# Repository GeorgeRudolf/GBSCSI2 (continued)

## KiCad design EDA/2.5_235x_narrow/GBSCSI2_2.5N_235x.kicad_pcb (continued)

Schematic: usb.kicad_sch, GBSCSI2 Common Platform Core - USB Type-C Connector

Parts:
C8: 100nF; C_0402_1005Metric; LCSC C307331
J3: GCT-4105; USB_C_Receptacle_HRO_TYPE-C-31-M-12; LCSC C2927038
R23, R24: 5.1kΩ; R_0402_1005Metric; LCSC C25905
U3: USB TVS; SOT-23-6; LCSC C2827654

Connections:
/Core Logic, Basic Controls/D+: J3.A6 (D+), J3.B6 (D+), U3.3 (I/O2), U3.4 (I/O2); also elsewhere on the board
/Core Logic, Basic Controls/D-: J3.A7 (D-), J3.B7 (D-), U3.1 (I/O1), U3.6 (I/O1); also elsewhere on the board
/Core Logic, Basic Controls/USB/CC1: J3.A5 (CC1), R24.1
/Core Logic, Basic Controls/USB/CC2: J3.B5 (CC2), R23.1
GND: C8.2, J3.A1 (GND), J3.A12 (GND), J3.B1 (GND), J3.B12 (GND), J3.S1 (SHIELD), R23.2, R24.2, U3.2 (GND); also elsewhere on the board
VBUS: C8.1, J3.A4 (VBUS), J3.A9 (VBUS), J3.B4 (VBUS), J3.B9 (VBUS), U3.5 (VBUS); also elsewhere on the board

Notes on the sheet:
USB-C Spec §3.2.1¶11

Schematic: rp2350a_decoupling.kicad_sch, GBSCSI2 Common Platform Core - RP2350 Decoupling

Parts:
C9, C11, C13, C14, C15, C16, C17, C18, C19: 100nF; C_0402_1005Metric; LCSC C307331
C10: 4.7μF; C_0402_1005Metric; LCSC C23733
C12: 1μF; C_0402_1005Metric; LCSC C52923

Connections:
+1.1V: C9.1, C10.1, C11.1; also elsewhere on the board
+3.3V: C12.1, C13.1, C14.1, C15.1, C16.1, C17.1, C18.1, C19.1; also elsewhere on the board
GND: C9.2, C10.2, C11.2, C12.2, C13.2, C14.2, C15.2, C16.2, C17.2, C18.2, C19.2; also elsewhere on the board

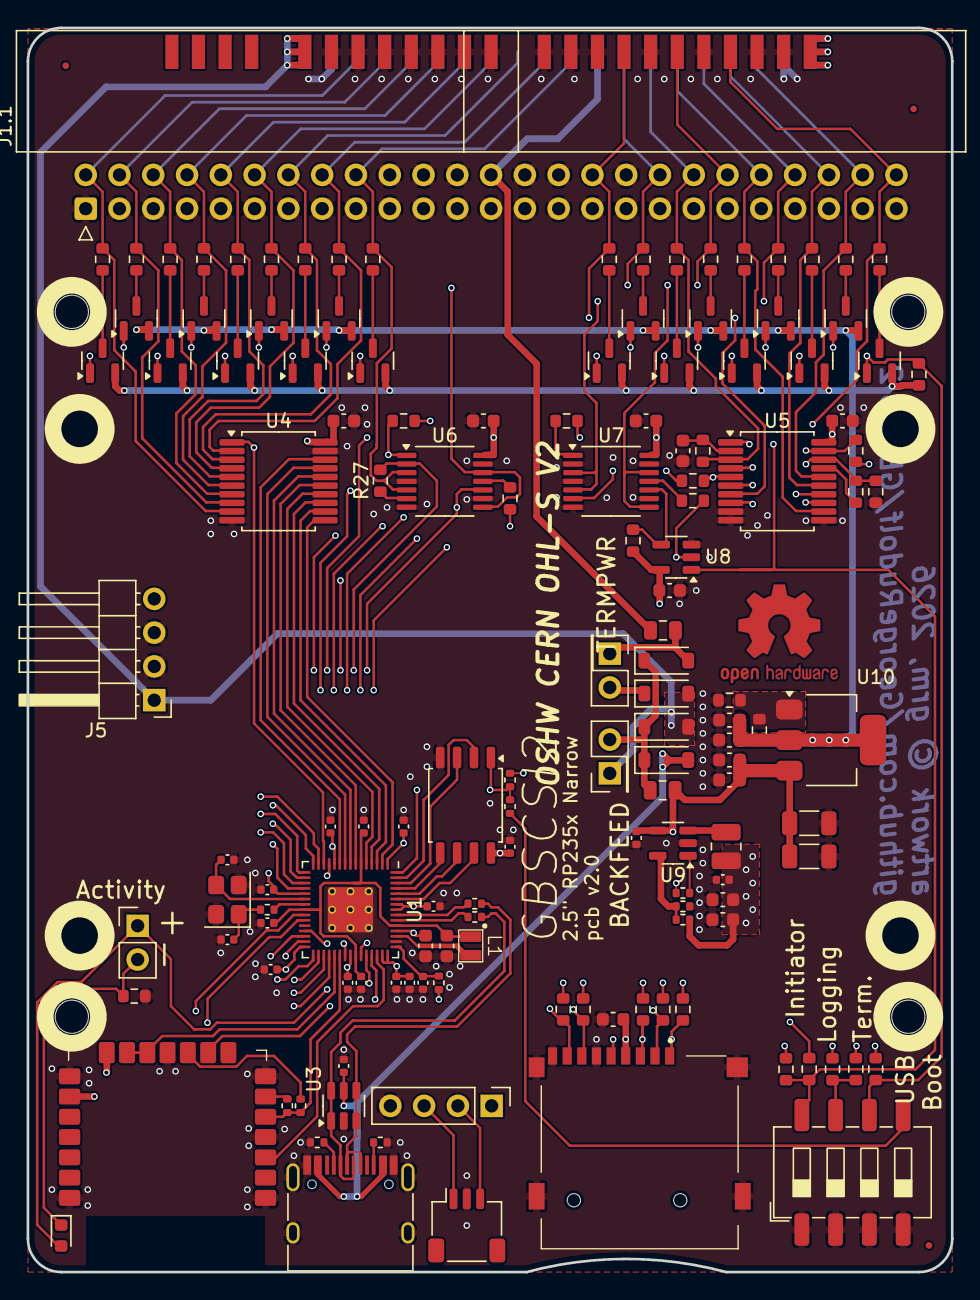
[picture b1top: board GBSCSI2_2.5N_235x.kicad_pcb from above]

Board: 4 copper layers, 69.5 x 93.5 mm, 145 parts (0 on the bottom side), 114 nets.

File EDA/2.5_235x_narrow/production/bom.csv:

Designator,Footprint,Quantity,Value,LCSC Part #
"C1, C4",0603,2,4.7μF,C19666
"C10, C27, C5",0402,3,4.7μF,C23733
"C11, C13, C14, C15, C16, C17, C18, C19, C28, C6, C8, C9",0402,12,100nF,C307331
C12,0402,1,1μF,C52923
"C2, C3",0402,2,15pF,C1548
"C20, C35",1206,2,47μF,C96123
C21,0603,1,12pF,C38523
"C22, C23, C24, C25, C26, C32, C33",0603,7,100nF,C14663
"C29, C30, C7",0603,3,10μF,C96446
"C31, C34",0603,2,1μF,C15849
"D1, D2, D3, D4",D_SOD-123,4,1N5819,C82544
D5,0603,1,YELLOW,C72038
"F1, F2",0805,2,1A,C468888
FID1,Fiducial_0.5mm_Mask1mm,1,Fiducial,N/A
J1,PinHeader_2x25-2_P2.00mm_straddle,1,SCSI_50-2P_2mm,N/A
J1.1,IDC-Header_2x25_P2.54mm_Horizontal,1,SCSI_50P_2.54mm,N/A
J2,TF01A,1,TF003,C5155563 
J3,USB_C_Receptacle_HRO_TYPE-C-31-M-12,1,GCT-4105,C2927038
J4,JST_SH_SM03B-SRSS-TB_1x03-1MP_P1.00mm_Horizontal,1,SM03B-SRSS-TB,C160403
J4.1,PinHeader_1x04_P2.54mm_Vertical,1,Conn_01x04,N/A
J5,PinHeader_1x04_P2.54mm_Horizontal,1,Conn_01x04,N/A
J6,PinHeader_1x02_P2.54mm_Vertical,1,Conn_01x02,N/A
"JP1, JP2",PinHeader_2x01_P2.54mm_Vertical,2,Jumper_2_Open,N/A
L1,L_Abracon_AOTA-B2016,1,3.3μH,C42411119
L2,1008,1,1μH,C5832356
M1,RPi_RM2,1,~,N/A
"Q1, Q10, Q11, Q12, Q13, Q14, Q15, Q16, Q17, Q18, Q2, Q3, Q4, Q5, Q6, Q7, Q8, Q9",SOT-23,18,AO3401A,C15127
"R1, R4",0402,2,1kΩ,C11702
"R10, R11, R12, R18, R19, R20, R21, R22, R29, R5, R6, R7, R8, R9",0603,14,4.7kΩ,C23162
"R13, R14, R17, R26, R27, R28, R30, R55",0603,8,1kΩ,C21190
"R15, R16, R3",0402,3,22Ω,C25092
R2,0402,1,4.7kΩ,C25900
"R23, R24",0402,2,5.1kΩ,C25905
"R25, R31, R32, R33, R34, R35, R36, R37, R38, R39, R40, R41, R42, R43, R44, R45, R46, R47, R48",0603,19,110Ω,C22781
"R49, R54",0402,2,10kΩ,C25744
R50,0402,1,442kΩ,C5101
R51,0402,1,100kΩ,C25741
R52,0603,1,0Ω,C21189
R53,0603,1,~,N/A
R56,0402,1,470Ω,
SW1,SW_DIP_SPSTx04_Slide_6.7x11.72mm_W8.61mm_P2.54mm_LowProfile,1,SW_DIP_x04,C5160841
U1,RP2350-QFN-60-1EP_7x7_P0.4mm_EP3.4x3.4mm_ThermalVias,1,RP235x_60QFN,C41378174
U10,SOT-223-3_TabPin2,1,AZ1117-2.85,C14791
U2,SOIC-8_5.23x5.23mm_P1.27mm,1,W25Q128JVS,C97521
U3,SOT-23-6,1,USB TVS,C2827654
"U4, U5",SSOP-20_5.3x7.2mm_P0.65mm,2,74LVTH245,C2652121
"U6, U7",TSSOP-14_4.4x5mm_P0.65mm,2,74LVTH125,C7042
U8,SOT-23-5,1,SN74AHC1G125DBVR,C7468
U9,SOT-23-5,1,TLV62569DBV,C141836
Y1,Crystal_SMD_3225-4Pin_3.2x2.5mm,1,12MHz,C20625731

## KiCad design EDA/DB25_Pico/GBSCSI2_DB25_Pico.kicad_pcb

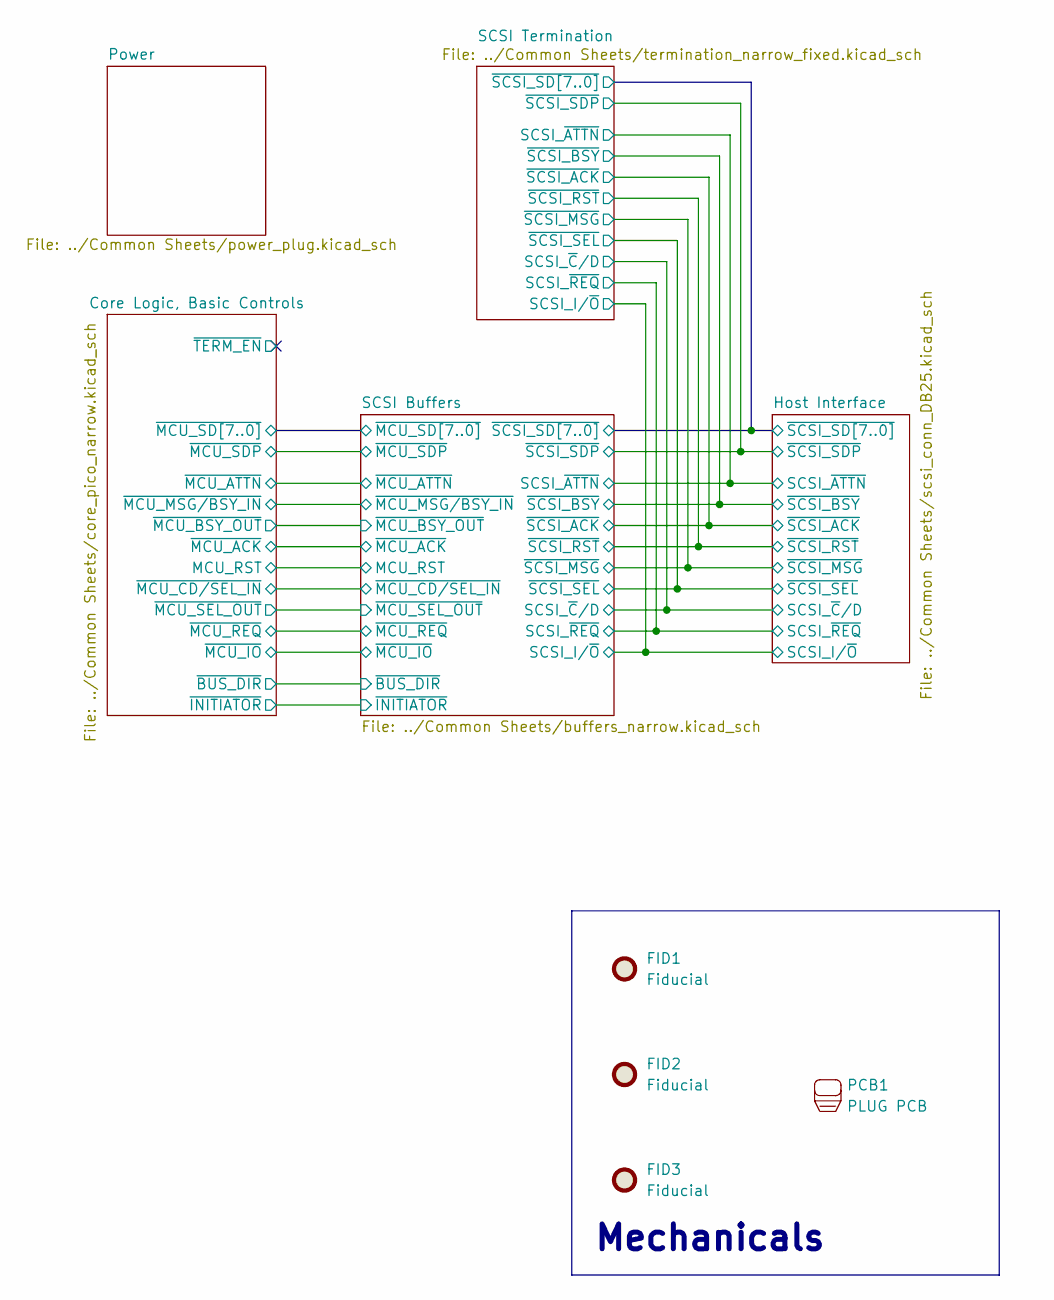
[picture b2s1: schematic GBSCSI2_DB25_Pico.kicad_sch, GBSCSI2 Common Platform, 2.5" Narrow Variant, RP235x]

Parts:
FID1, FID2, FID3: Fiducial; Fiducial_0.5mm_Mask1mm; LCSC N/A
PCB1: PLUG PCB; GBSCSI2_PLUG_PCB

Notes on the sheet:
Mechanicals

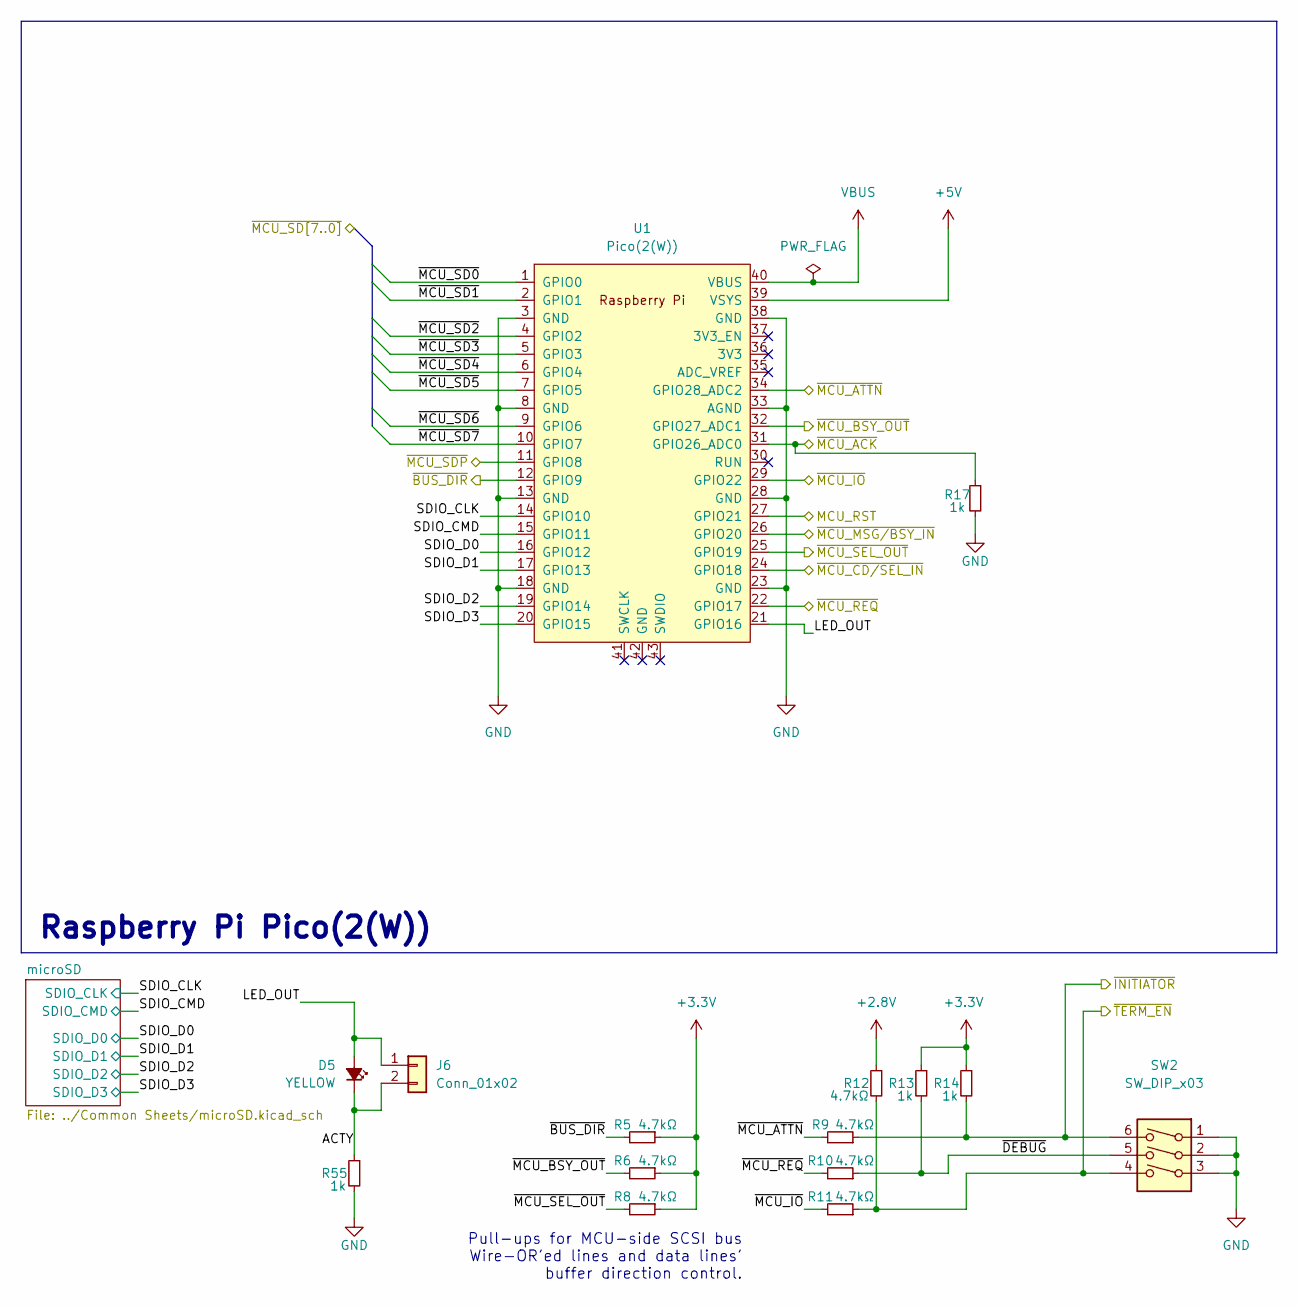
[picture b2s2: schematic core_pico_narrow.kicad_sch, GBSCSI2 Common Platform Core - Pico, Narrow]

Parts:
D5: YELLOW; LED_0603_1608Metric; LCSC C72038
J6: Conn_01x02; PinHeader_1x02_P2.54mm_Vertical; LCSC N/A
R5, R6, R8, R9, R10, R11, R12: 4.7kΩ; R_0603_1608Metric; LCSC C23162
R13, R14, R17, R55: 1k; R_0603_1608Metric; LCSC C21190
SW2: SW_DIP_x03; SW_DIP_SPSTx03_Slide_6.7x9.18mm_W8.61mm_P2.54mm_LowProfile; LCSC C2842910
U1: Pico(2(W)); RPi_Pico_W_SMD; LCSC C7203003

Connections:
+2.8V: R12.1; also elsewhere on the board
+3.3V: R5.1, R6.1, R8.1, R13.1, R14.1; also elsewhere on the board
+5V: U1.39 (VSYS); also elsewhere on the board
/Core Logic, Basic Controls/ACTY: D5.1 (K), J6.2, R55.1
/Core Logic, Basic Controls/LED_OUT: D5.2 (A), J6.1, U1.21 (GPIO16)
/Core Logic, Basic Controls/MCU_RST: U1.27 (GPIO21); also elsewhere on the board
/Core Logic, Basic Controls/SDIO_CLK: U1.14 (GPIO10); also elsewhere on the board
/Core Logic, Basic Controls/SDIO_CMD: U1.15 (GPIO11); also elsewhere on the board
/Core Logic, Basic Controls/SDIO_D0: U1.16 (GPIO12); also elsewhere on the board
/Core Logic, Basic Controls/SDIO_D1: U1.17 (GPIO13); also elsewhere on the board
/Core Logic, Basic Controls/SDIO_D2: U1.19 (GPIO14); also elsewhere on the board
/Core Logic, Basic Controls/SDIO_D3: U1.20 (GPIO15); also elsewhere on the board
/Core Logic, Basic Controls/~BUS_DIR: R5.2, U1.12 (GPIO9); also elsewhere on the board
/Core Logic, Basic Controls/~DEBUG: R10.1, R13.2, SW2.5
/Core Logic, Basic Controls/~INITIATOR: R9.1, R14.2, SW2.6; also elsewhere on the board
/Core Logic, Basic Controls/~MCU_ACK: R17.1, U1.31 (GPIO26_ADC0); also elsewhere on the board
/Core Logic, Basic Controls/~MCU_ATTN: R9.2, U1.34 (GPIO28_ADC2); also elsewhere on the board
/Core Logic, Basic Controls/~MCU_BSY_OUT: R6.2, U1.32 (GPIO27_ADC1); also elsewhere on the board
/Core Logic, Basic Controls/~MCU_CD/SEL_IN: U1.24 (GPIO18); also elsewhere on the board
/Core Logic, Basic Controls/~MCU_IO: R11.2, U1.29 (GPIO22); also elsewhere on the board
/Core Logic, Basic Controls/~MCU_MSG/BSY_IN: U1.26 (GPIO20); also elsewhere on the board
/Core Logic, Basic Controls/~MCU_REQ: R10.2, U1.22 (GPIO17); also elsewhere on the board
/Core Logic, Basic Controls/~MCU_SD0: U1.1 (GPIO0); also elsewhere on the board
/Core Logic, Basic Controls/~MCU_SD1: U1.2 (GPIO1); also elsewhere on the board
/Core Logic, Basic Controls/~MCU_SD2: U1.4 (GPIO2); also elsewhere on the board
/Core Logic, Basic Controls/~MCU_SD3: U1.5 (GPIO3); also elsewhere on the board
/Core Logic, Basic Controls/~MCU_SD4: U1.6 (GPIO4); also elsewhere on the board
/Core Logic, Basic Controls/~MCU_SD5: U1.7 (GPIO5); also elsewhere on the board
/Core Logic, Basic Controls/~MCU_SD6: U1.9 (GPIO6); also elsewhere on the board
/Core Logic, Basic Controls/~MCU_SD7: U1.10 (GPIO7); also elsewhere on the board
/Core Logic, Basic Controls/~MCU_SDP: U1.11 (GPIO8); also elsewhere on the board
/Core Logic, Basic Controls/~MCU_SEL_OUT: R8.2, U1.25 (GPIO19); also elsewhere on the board
/Core Logic, Basic Controls/~TERM_EN: R11.1, R12.2, SW2.4
GND: R17.2, R55.2, SW2.1, SW2.2, SW2.3, U1.3 (GND), U1.8 (GND), U1.13 (GND), U1.18 (GND), U1.23 (GND), U1.28 (GND), U1.33 (AGND), U1.38 (GND); also elsewhere on the board
VBUS: U1.40 (VBUS); also elsewhere on the board

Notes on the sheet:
Pull-ups for MCU-side SCSI bus Wire-OR'ed lines and data lines' buffer direction control.
Raspberry Pi Pico(2(W))

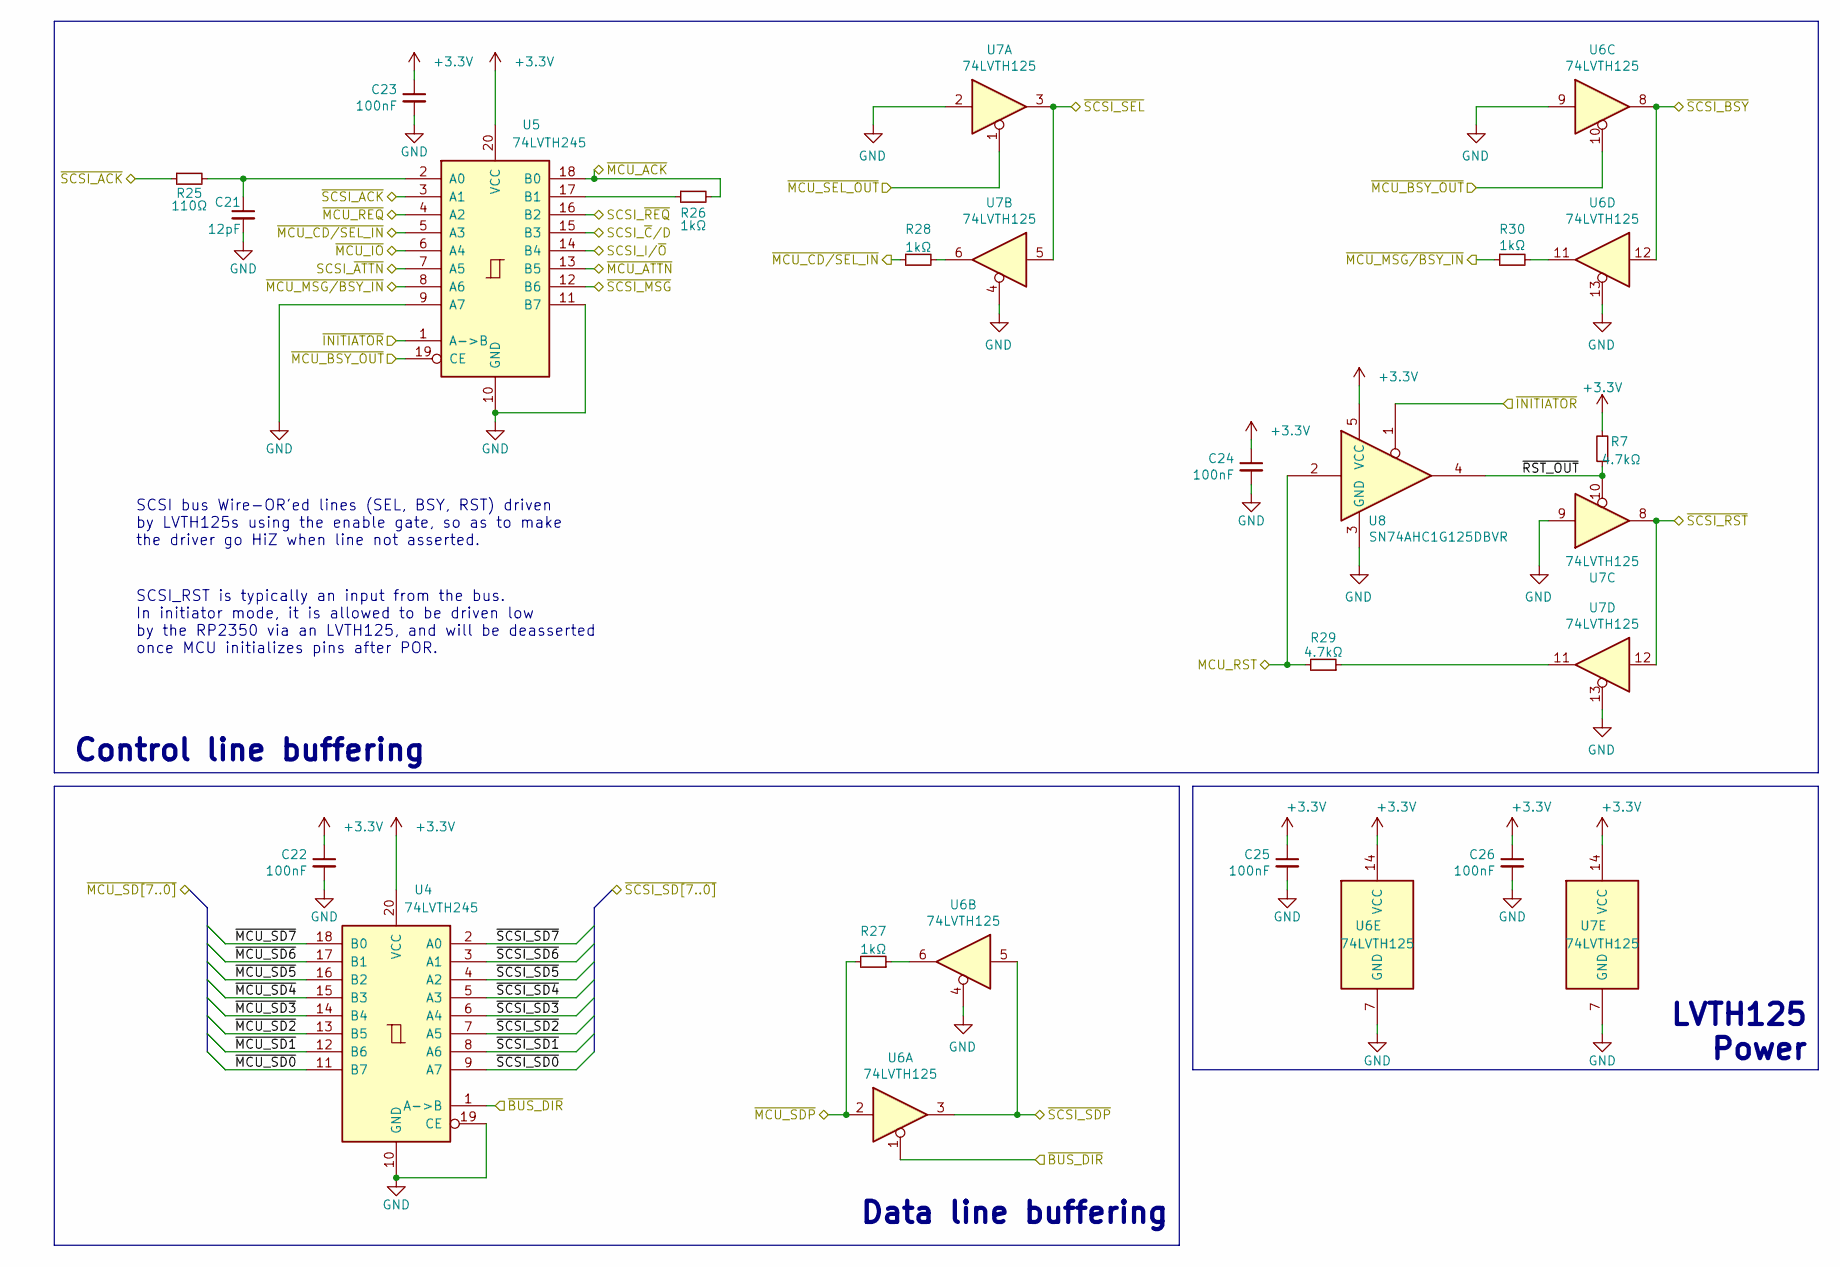
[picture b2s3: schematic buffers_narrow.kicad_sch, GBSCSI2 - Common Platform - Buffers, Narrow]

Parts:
C21: 12pF; C_0603_1608Metric; LCSC C38523
C22, C23, C24, C25, C26: 100nF; C_0603_1608Metric; LCSC C14663
R7, R29: 4.7kΩ; R_0603_1608Metric; LCSC C23162
R25: 110Ω; R_0603_1608Metric; LCSC C22781
R26, R27, R28, R30: 1kΩ; R_0603_1608Metric; LCSC C21190
U4, U5: 74LVTH245; SSOP-20_5.3x7.2mm_P0.65mm; LCSC C2652121
U6, U7: 74LVTH125; TSSOP-14_4.4x5mm_P0.65mm; LCSC C7042
U8: SN74AHC1G125DBVR; SOT-23-5; LCSC C7468

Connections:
+3.3V: C22.1, C23.1, C24.1, C25.1, C26.1, R7.2, U4.20 (VCC), U5.20 (VCC), U6.14 (VCC), U7.14 (VCC), U8.5 (VCC); also elsewhere on the board
/Core Logic, Basic Controls/MCU_RST: R29.2, U8.2; also elsewhere on the board
/Core Logic, Basic Controls/~BUS_DIR: U4.1 (A->B), U6.1; also elsewhere on the board
/Core Logic, Basic Controls/~INITIATOR: U5.1 (A->B), U8.1; also elsewhere on the board
/Core Logic, Basic Controls/~MCU_ACK: R26.2, U5.18 (B0); also elsewhere on the board
/Core Logic, Basic Controls/~MCU_ATTN: U5.13 (B5); also elsewhere on the board
/Core Logic, Basic Controls/~MCU_BSY_OUT: U5.19 (CE), U6.10; also elsewhere on the board
/Core Logic, Basic Controls/~MCU_CD/SEL_IN: R28.1, U5.5 (A3); also elsewhere on the board
/Core Logic, Basic Controls/~MCU_IO: U5.6 (A4); also elsewhere on the board
/Core Logic, Basic Controls/~MCU_MSG/BSY_IN: R30.1, U5.8 (A6); also elsewhere on the board
/Core Logic, Basic Controls/~MCU_REQ: U5.4 (A2); also elsewhere on the board
/Core Logic, Basic Controls/~MCU_SD0: U4.11 (B7); also elsewhere on the board
/Core Logic, Basic Controls/~MCU_SD1: U4.12 (B6); also elsewhere on the board
/Core Logic, Basic Controls/~MCU_SD2: U4.13 (B5); also elsewhere on the board
/Core Logic, Basic Controls/~MCU_SD3: U4.14 (B4); also elsewhere on the board
/Core Logic, Basic Controls/~MCU_SD4: U4.15 (B3); also elsewhere on the board
/Core Logic, Basic Controls/~MCU_SD5: U4.16 (B2); also elsewhere on the board
/Core Logic, Basic Controls/~MCU_SD6: U4.17 (B1); also elsewhere on the board
/Core Logic, Basic Controls/~MCU_SD7: U4.18 (B0); also elsewhere on the board
/Core Logic, Basic Controls/~MCU_SDP: R27.2, U6.2; also elsewhere on the board
/Core Logic, Basic Controls/~MCU_SEL_OUT: U7.1; also elsewhere on the board
/Host Interface/SCSI_I/~O: U5.14 (B4); also elsewhere on the board
/Host Interface/SCSI_~ATTN: U5.7 (A5); also elsewhere on the board
/Host Interface/SCSI_~C/D: U5.15 (B3); also elsewhere on the board
/Host Interface/SCSI_~REQ: U5.16 (B2); also elsewhere on the board
/Host Interface/~SCSI_ACK: R25.1, U5.3 (A1); also elsewhere on the board
/Host Interface/~SCSI_BSY: U6.8, U6.12; also elsewhere on the board
/Host Interface/~SCSI_MSG: U5.12 (B6); also elsewhere on the board
/Host Interface/~SCSI_RST: U7.8, U7.12; also elsewhere on the board
/Host Interface/~SCSI_SD0: U4.9 (A7); also elsewhere on the board
/Host Interface/~SCSI_SD1: U4.8 (A6); also elsewhere on the board
/Host Interface/~SCSI_SD2: U4.7 (A5); also elsewhere on the board
/Host Interface/~SCSI_SD3: U4.6 (A4); also elsewhere on the board
/Host Interface/~SCSI_SD4: U4.5 (A3); also elsewhere on the board
/Host Interface/~SCSI_SD5: U4.4 (A2); also elsewhere on the board
/Host Interface/~SCSI_SD6: U4.3 (A1); also elsewhere on the board
/Host Interface/~SCSI_SD7: U4.2 (A0); also elsewhere on the board
/Host Interface/~SCSI_SDP: U6.3, U6.5; also elsewhere on the board
/Host Interface/~SCSI_SEL: U7.3, U7.5; also elsewhere on the board
/SCSI Buffers/~RST_OUT: R7.1, U7.10, U8.4
GND: C21.2, C22.2, C23.2, C24.2, C25.2, C26.2, U4.10 (GND), U4.19 (CE), U5.9 (A7), U5.10 (GND), U5.11 (B7), U6.4, U6.7 (GND), U6.9, U6.13, U7.2, U7.4, U7.7 (GND), U7.9, U7.13, U8.3 (GND); also elsewhere on the board
unnamed: R27.1, U6.6
unnamed: R28.2, U7.6
unnamed: R29.1, U7.11
unnamed: R30.2, U6.11
unnamed: C21.1, R25.2, U5.2 (A0)
unnamed: R26.1, U5.17 (B1)

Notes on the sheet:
Control line buffering
SCSI_RST is typically an input from the bus. In initiator mode, it is allowed to be driven low by the RP2350 via an LVTH125, and will be deasserted once MCU initializes pins after POR.
LVTH125 Power
SCSI bus Wire-OR'ed lines (SEL, BSY, RST) driven by LVTH125s using the enable gate, so as to make the driver go HiZ when line not asserted.
Data line buffering

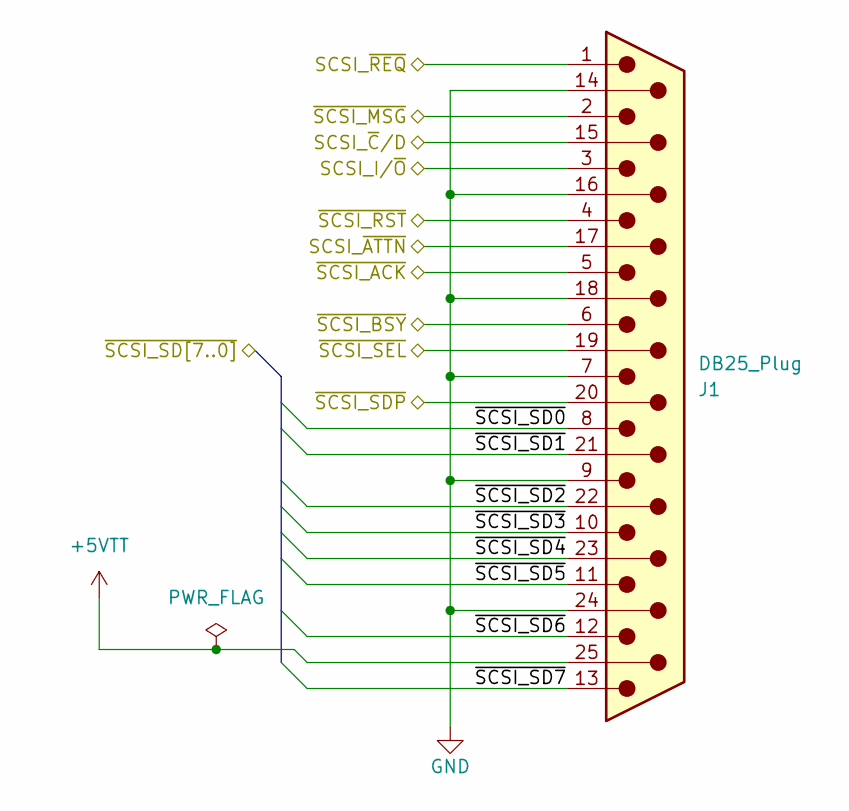
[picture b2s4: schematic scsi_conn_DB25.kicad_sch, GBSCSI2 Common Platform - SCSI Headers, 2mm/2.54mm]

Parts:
J1: DB25_Plug; DSUB-25_Male_EdgeMount_P2.77mm; LCSC N/A

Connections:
+5VTT: J1.25; also elsewhere on the board
/Host Interface/SCSI_I/~O: J1.3; also elsewhere on the board
/Host Interface/SCSI_~ATTN: J1.17; also elsewhere on the board
/Host Interface/SCSI_~C/D: J1.15; also elsewhere on the board
/Host Interface/SCSI_~REQ: J1.1; also elsewhere on the board
/Host Interface/~SCSI_ACK: J1.5; also elsewhere on the board
/Host Interface/~SCSI_BSY: J1.6; also elsewhere on the board
/Host Interface/~SCSI_MSG: J1.2; also elsewhere on the board
/Host Interface/~SCSI_RST: J1.4; also elsewhere on the board
/Host Interface/~SCSI_SD0: J1.8; also elsewhere on the board
/Host Interface/~SCSI_SD1: J1.21; also elsewhere on the board
/Host Interface/~SCSI_SD2: J1.22; also elsewhere on the board
/Host Interface/~SCSI_SD3: J1.10; also elsewhere on the board
/Host Interface/~SCSI_SD4: J1.23; also elsewhere on the board
/Host Interface/~SCSI_SD5: J1.11; also elsewhere on the board
/Host Interface/~SCSI_SD6: J1.12; also elsewhere on the board
/Host Interface/~SCSI_SD7: J1.13; also elsewhere on the board
/Host Interface/~SCSI_SDP: J1.20; also elsewhere on the board
/Host Interface/~SCSI_SEL: J1.19; also elsewhere on the board
GND: J1.7, J1.9, J1.14, J1.16, J1.18, J1.24; also elsewhere on the board

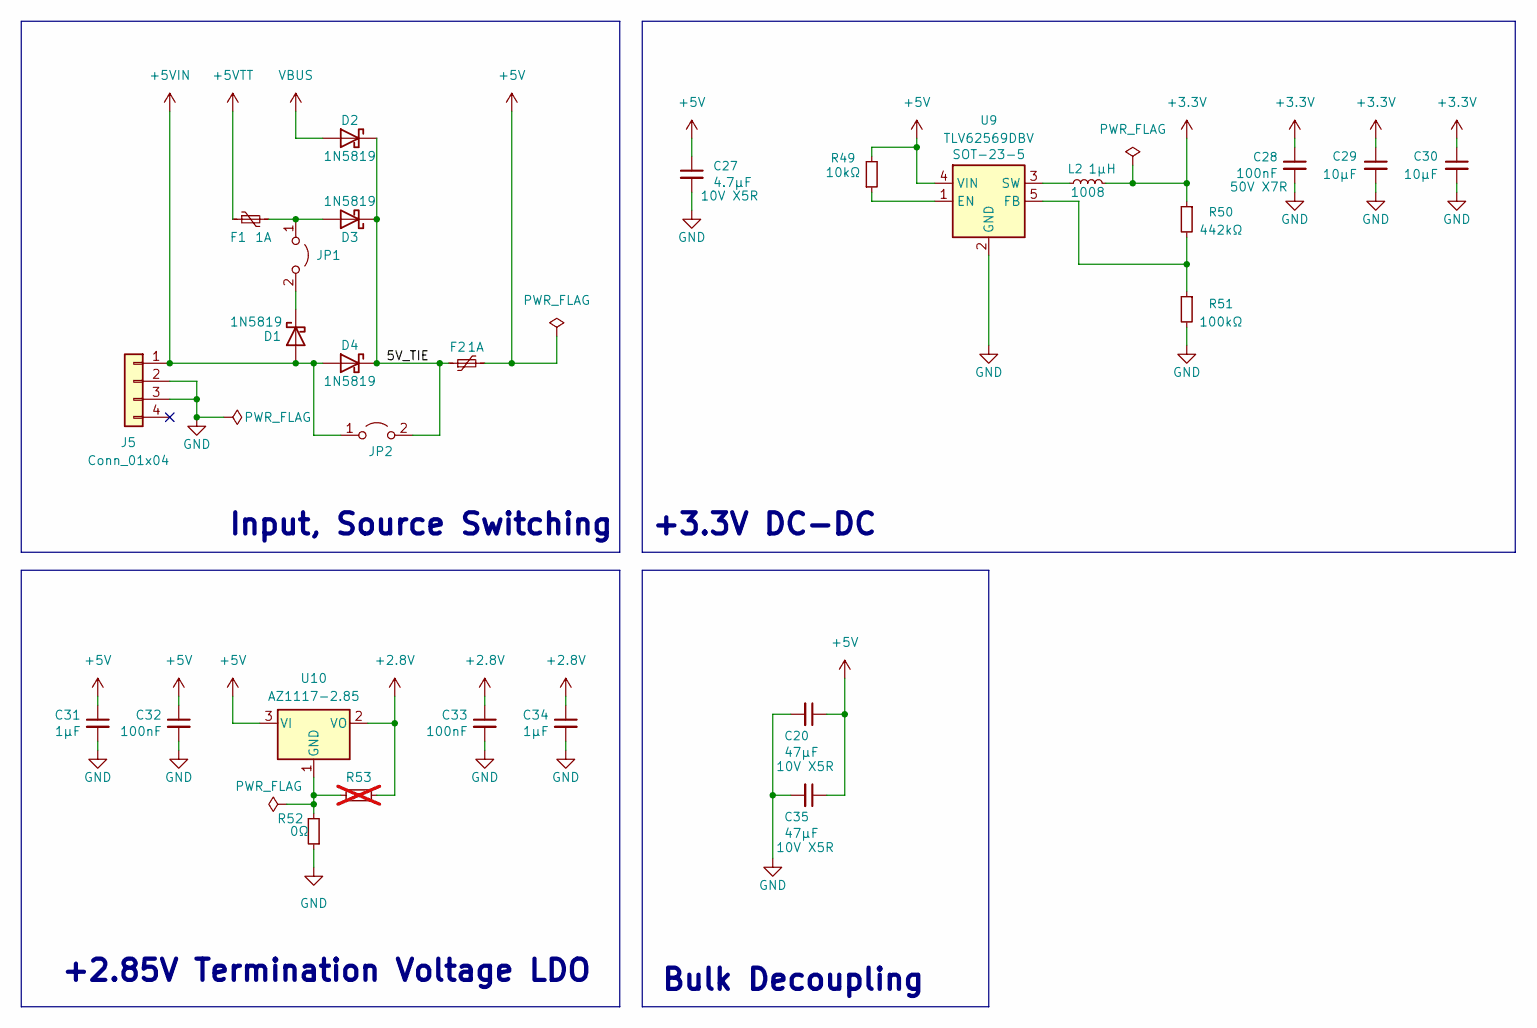
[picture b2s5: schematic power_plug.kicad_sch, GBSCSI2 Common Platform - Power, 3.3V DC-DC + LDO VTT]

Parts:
C20, C35: 47μF; C_1206_3216Metric; LCSC C96123
C27: 4.7μF; C_0402_1005Metric; LCSC C23733
C28: 100nF; C_0402_1005Metric; LCSC C307331
C29, C30: 10μF; C_0603_1608Metric; LCSC C96446
C31, C34: 1μF; C_0603_1608Metric; LCSC C15849
C32, C33: 100nF; C_0603_1608Metric; LCSC C14663
D1, D2, D3, D4: 1N5819; D_SOD-123; LCSC C191023
F1, F2: 1A; Fuse_0805_2012Metric; LCSC C468888
J5: Conn_01x04; PinHeader_1x04_P2.54mm_Horizontal; LCSC N/A
JP1, JP2: Jumper_2_Open; PinHeader_2x01_P2.54mm_Vertical; LCSC N/A
L2: 1μH; L_1008_2520Metric; LCSC C5832356
R49: 10kΩ; R_0402_1005Metric; LCSC C25744
R50: 442kΩ; R_0402_1005Metric; LCSC C5101
R51: 100kΩ; R_0402_1005Metric; LCSC C25741
R52: 0Ω; R_0603_1608Metric; LCSC C21189
R53: R_0603_1608Metric; LCSC N/A; not fitted
U9: TLV62569DBV; SOT-23-5; LCSC C141836
U10: AZ1117-2.85; SOT-223-3_TabPin2; LCSC C14791

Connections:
+2.8V: C33.1, C34.1, R53.2, U10.2 (VO); also elsewhere on the board
+3.3V: C28.1, C29.1, C30.1, L2.2, R50.1; also elsewhere on the board
+5V: C20.1, C27.1, C31.1, C32.1, C35.1, F2.2, R49.2, U9.4 (VIN), U10.3 (VI); also elsewhere on the board
+5VIN: D1.2 (A), D4.2 (A), J5.1, JP2.1 (A)
+5VTT: F1.1; also elsewhere on the board
/Power/5V_TIE: D2.1 (K), D3.1 (K), D4.1 (K), F2.1, JP2.2 (B)
GND: C20.2, C27.2, C28.2, C29.2, C30.2, C31.2, C32.2, C33.2, C34.2, C35.2, J5.2, J5.3, R51.2, R52.1, U9.2 (GND); also elsewhere on the board
unnamed: D1.1 (K), JP1.2 (B)
unnamed: D3.2 (A), F1.2, JP1.1 (A)
unnamed: R49.1, U9.1 (EN)
unnamed: R50.2, R51.1, U9.5 (FB)
unnamed: L2.1, U9.3 (SW)
unnamed: R52.2, R53.1, U10.1 (GND)
VBUS: D2.2 (A); also elsewhere on the board

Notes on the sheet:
+2.85V Termination Voltage LDO
+3.3V DC-DC
Bulk Decoupling
Input, Source Switching

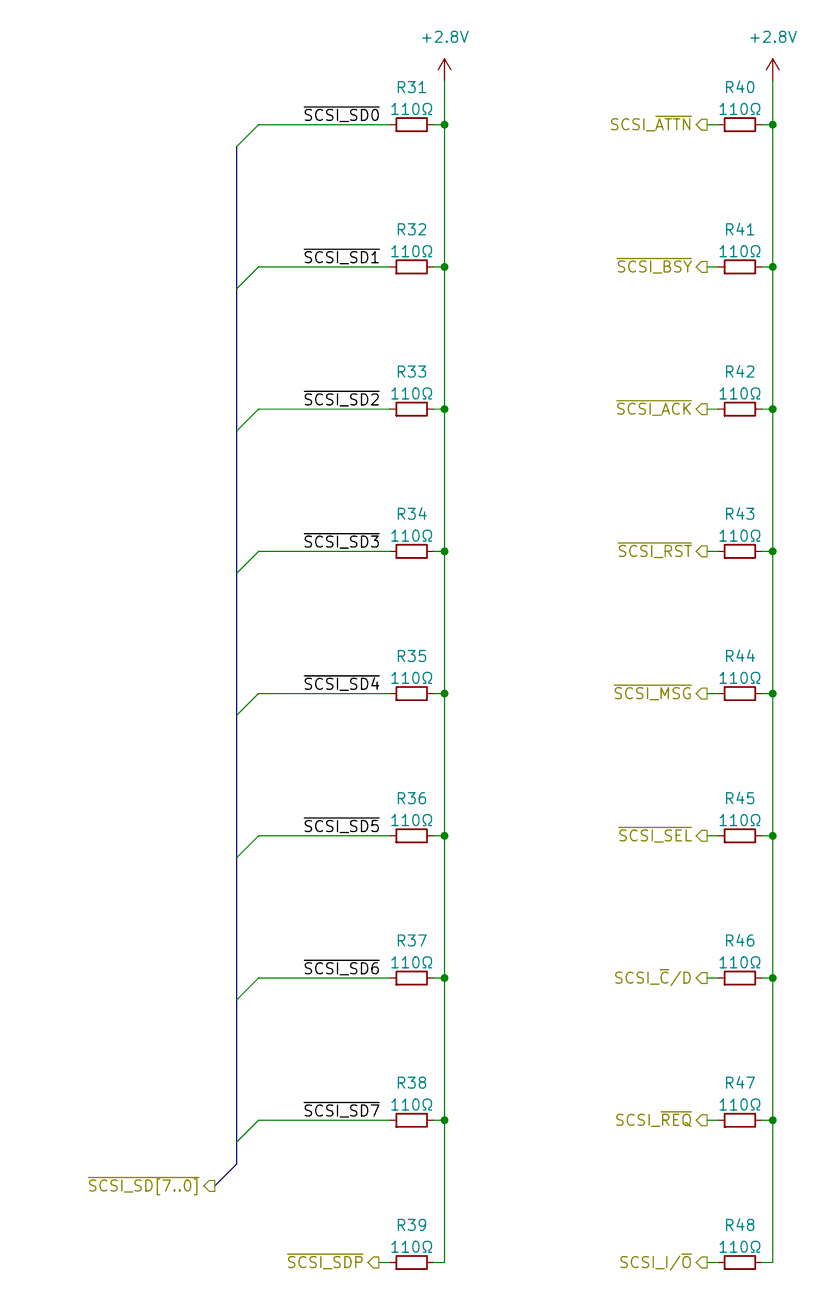
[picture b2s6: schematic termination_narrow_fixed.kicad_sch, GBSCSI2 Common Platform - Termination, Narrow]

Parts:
R31, R32, R33, R34, R35, R36, R37, R38, R39, R40, R41, R42, R43, R44, R45, R46, R47, R48: 110Ω; R_0603_1608Metric; LCSC C22781

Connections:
+2.8V: R31.2, R32.2, R33.2, R34.2, R35.2, R36.2, R37.2, R38.2, R39.2, R40.2, R41.2, R42.2, R43.2, R44.2, R45.2, R46.2, R47.2, R48.2; also elsewhere on the board
/Host Interface/SCSI_I/~O: R48.1; also elsewhere on the board
/Host Interface/SCSI_~ATTN: R40.1; also elsewhere on the board
/Host Interface/SCSI_~C/D: R46.1; also elsewhere on the board
/Host Interface/SCSI_~REQ: R47.1; also elsewhere on the board
/Host Interface/~SCSI_ACK: R42.1; also elsewhere on the board
/Host Interface/~SCSI_BSY: R41.1; also elsewhere on the board
/Host Interface/~SCSI_MSG: R44.1; also elsewhere on the board
/Host Interface/~SCSI_RST: R43.1; also elsewhere on the board
/Host Interface/~SCSI_SD0: R31.1; also elsewhere on the board
/Host Interface/~SCSI_SD1: R32.1; also elsewhere on the board
/Host Interface/~SCSI_SD2: R33.1; also elsewhere on the board
/Host Interface/~SCSI_SD3: R34.1; also elsewhere on the board
/Host Interface/~SCSI_SD4: R35.1; also elsewhere on the board
/Host Interface/~SCSI_SD5: R36.1; also elsewhere on the board
/Host Interface/~SCSI_SD6: R37.1; also elsewhere on the board
/Host Interface/~SCSI_SD7: R38.1; also elsewhere on the board
/Host Interface/~SCSI_SDP: R39.1; also elsewhere on the board
/Host Interface/~SCSI_SEL: R45.1; also elsewhere on the board

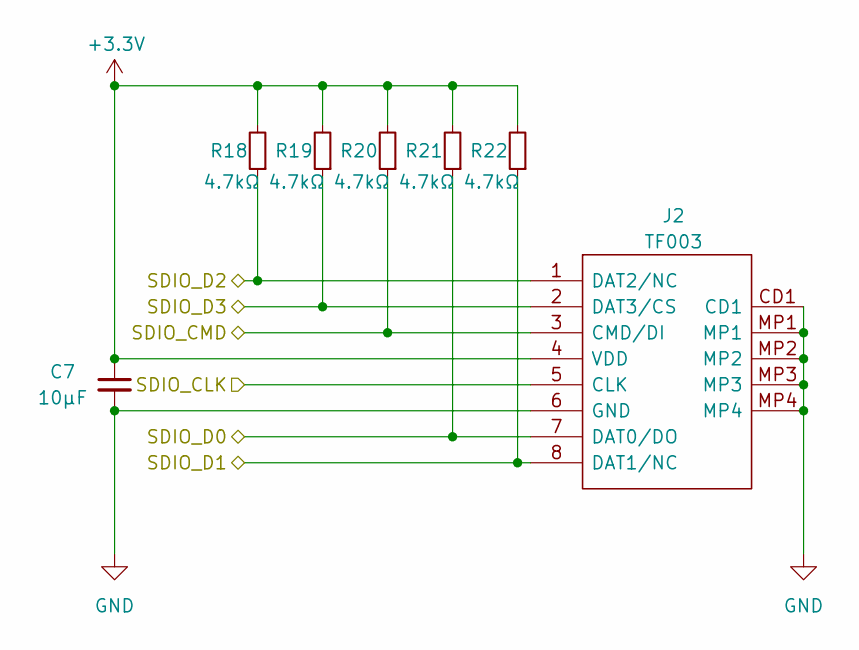
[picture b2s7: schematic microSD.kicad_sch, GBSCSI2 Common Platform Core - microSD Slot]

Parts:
C7: 10μF; C_0603_1608Metric; LCSC C96446
J2: TF003; TF01A; LCSC C5155563
R18, R19, R20, R21, R22: 4.7kΩ; R_0603_1608Metric; LCSC C23162

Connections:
+3.3V: C7.1, J2.4 (VDD), R18.2, R19.2, R20.2, R21.2, R22.2; also elsewhere on the board
/Core Logic, Basic Controls/SDIO_CLK: J2.5 (CLK); also elsewhere on the board
/Core Logic, Basic Controls/SDIO_CMD: J2.3 (CMD/DI), R20.1; also elsewhere on the board
/Core Logic, Basic Controls/SDIO_D0: J2.7 (DAT0/DO), R21.1; also elsewhere on the board
/Core Logic, Basic Controls/SDIO_D1: J2.8 (DAT1/NC), R22.1; also elsewhere on the board
/Core Logic, Basic Controls/SDIO_D2: J2.1 (DAT2/NC), R18.1; also elsewhere on the board
/Core Logic, Basic Controls/SDIO_D3: J2.2 (DAT3/CS), R19.1; also elsewhere on the board
GND: C7.2, J2.6 (GND), J2.CD1, J2.MP1, J2.MP2, J2.MP3, J2.MP4; also elsewhere on the board

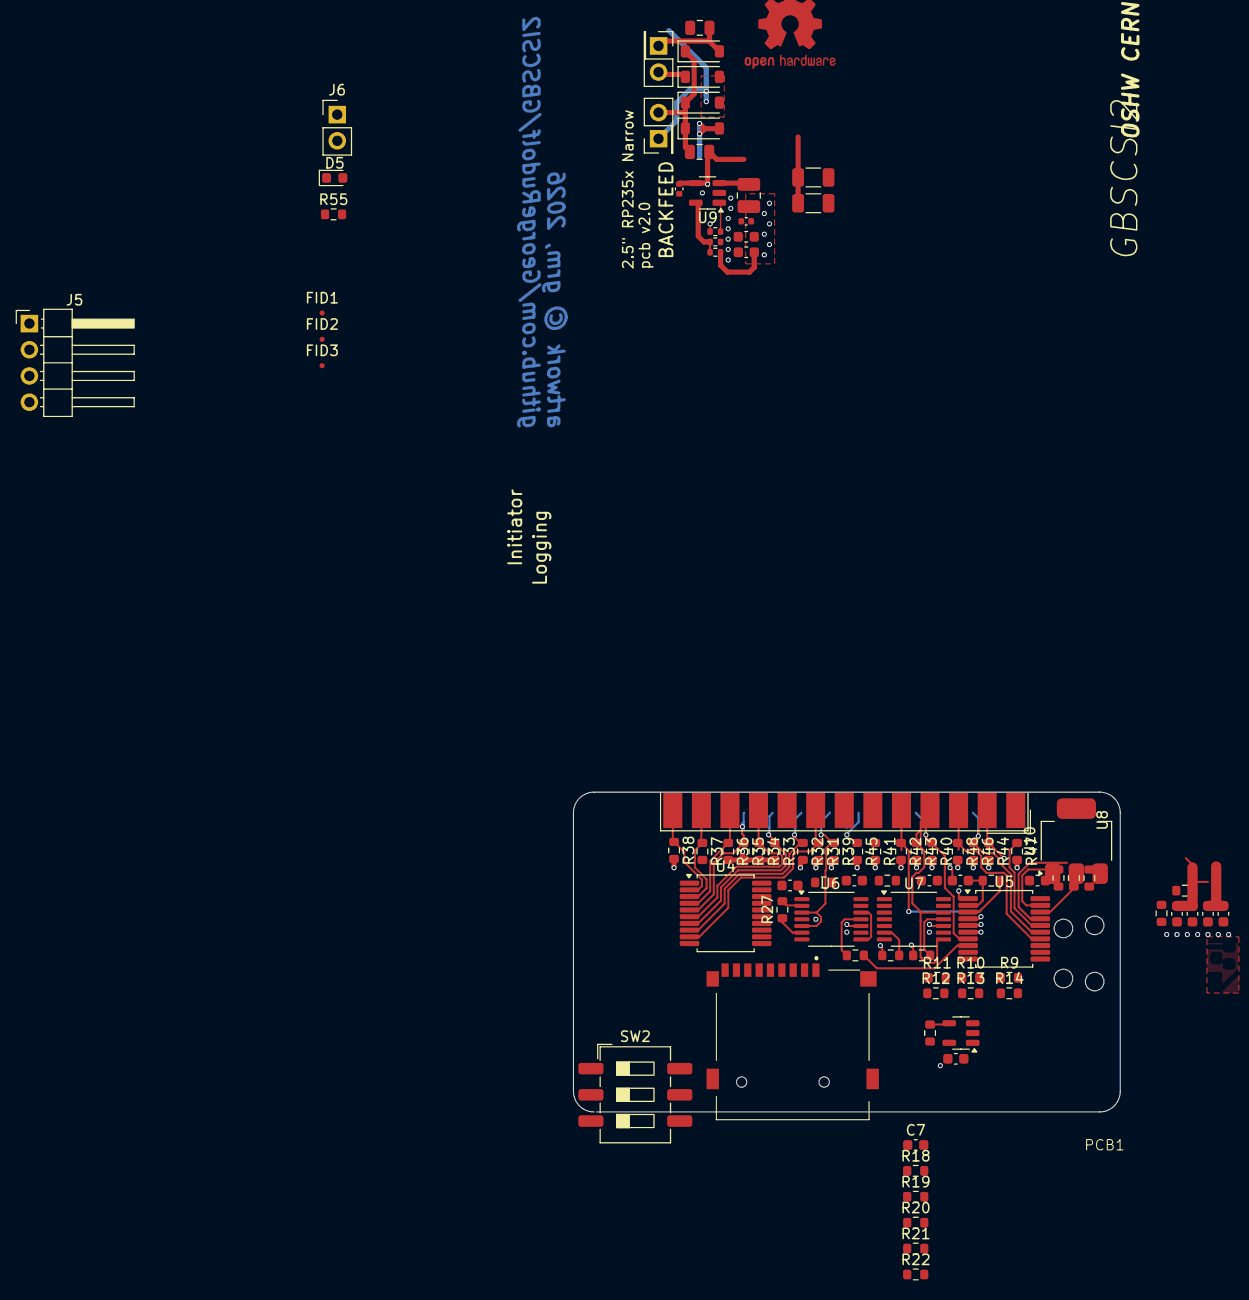
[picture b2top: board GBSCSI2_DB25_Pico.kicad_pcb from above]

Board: 4 copper layers, 53.0 x 31.0 mm, 90 parts (1 on the bottom side), 69 nets.
